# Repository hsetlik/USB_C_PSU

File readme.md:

# USB-C and li-ion power supply

I designed this little power supply board for my ongoing polyphonic synth project. Like most analog synths it needs a +/-12V supply, as well as a 3.3V supply to run a microcontroller and some other digital bits and pieces. It doesn't consume a crazy amount of power, so I thought a built-in battery and the ability to power the synth over USB-C would be nice features. As power supplies go it's a bit complicated, but the circuit is made up of six basic blocks which are each simple enough on their own so I'll go through each one below.

The KiCad files are for both the schematic and the PCB are in this repo along with a PDF of the schematic. There's an interactive BOM file inside the "bom" directory as well.

## Block 1: USB-C connector and PD negotiation

Throughout the revisions of this board I learned the hard way that power over USB-C isn't as simple as routing the VBUS pin to a power input. Devices that recieve power via USB-C PD (power delivery) must "negotiate" with the power source via the connector's two CC pins to request the needed voltage and current. A simple solution here is to connect CC1 and CC2 to ground each through their own 5.1k resistor. This, however limits the device to 500mA at 5V. In order to negotiate our target max power of 3A at 5 volts, we can use a dedicated IC like the [CYPD3177](https://www.infineon.com/dgdl/Infineon-EZ-PD_BCR_Datasheet_USB_Type-C_Port_Controller_for_Power_Sinks-DataSheet-v03_00-EN.pdf?fileId=8ac78c8c7d0d8da4017d0ee7ce9d70ad), which connects to our CC pins and negotiates for voltage and current values which are set by some resistor dividers. [This video](https://www.youtube.com/watch?v=W13HNsoHj7A&t=1458s) by Phil's Lab on YouTube is a great explanation of this IC and how to work with USB-C in general. The IC operates a MOSFET load switch (Q102 on the schematic) to connect the input 5V line to our VDD net when negotiation is successful.

## Block 2: Battery charger

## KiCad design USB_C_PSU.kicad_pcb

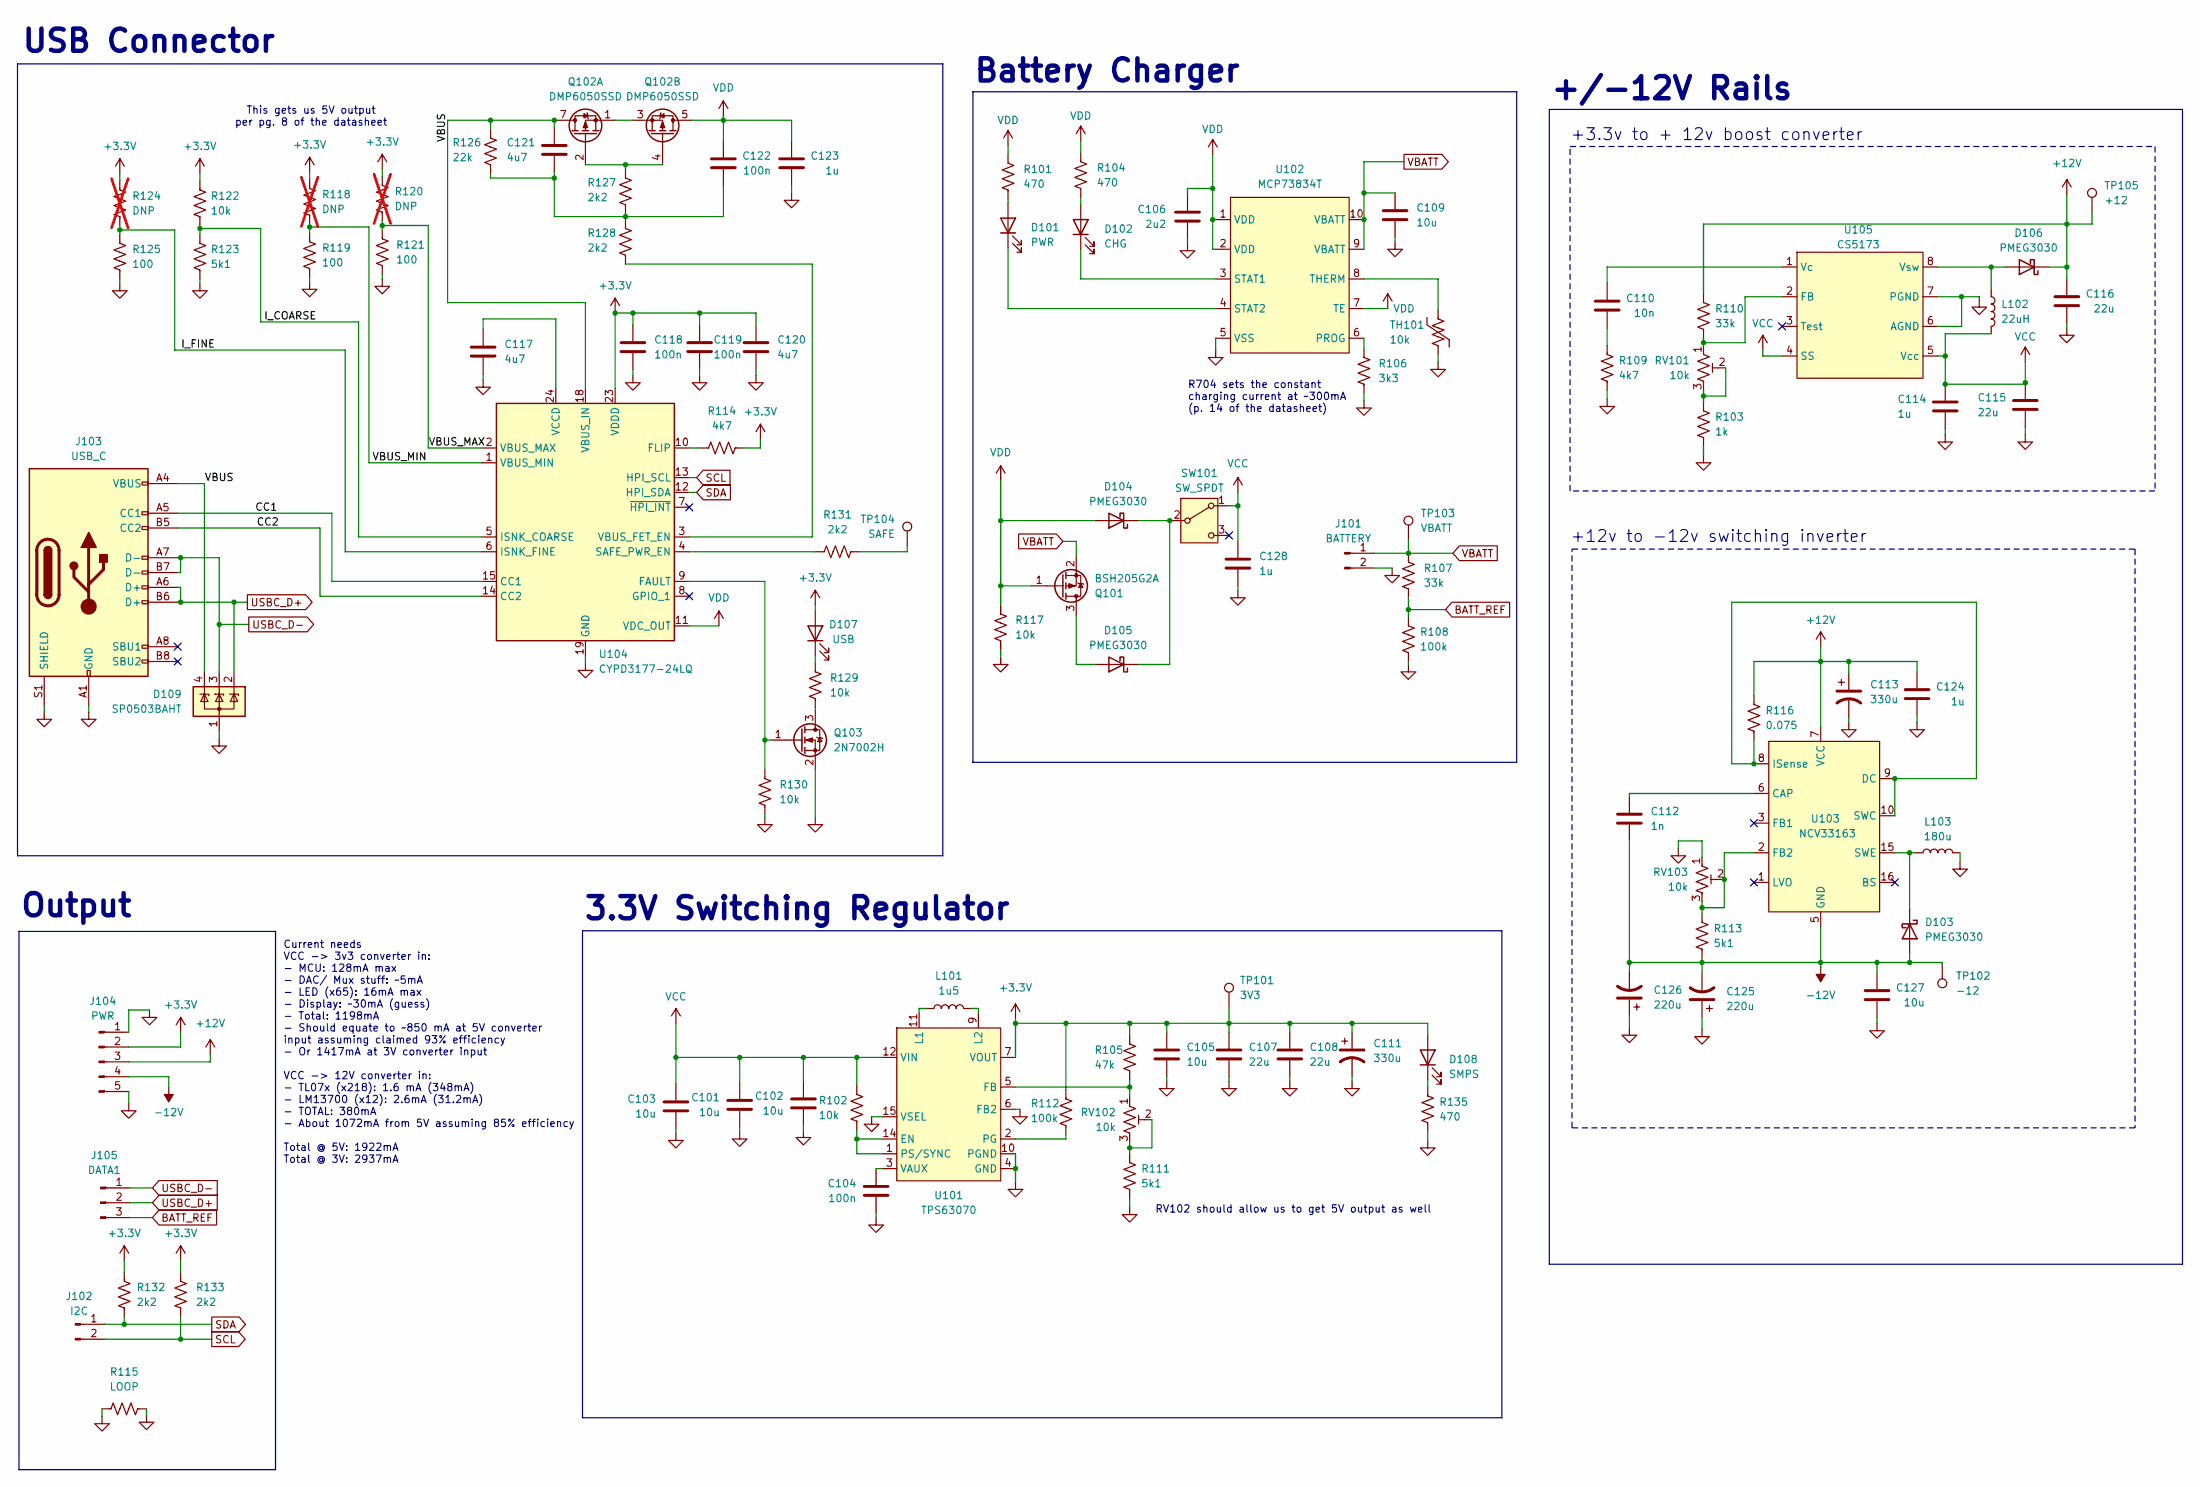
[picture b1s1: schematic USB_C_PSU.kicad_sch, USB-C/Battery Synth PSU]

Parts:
C101, C102, C103, C105, C109, C127: 10u; C_0805_2012Metric
C104, C118, C119, C122: 100n; C_0805_2012Metric
C106: 2u2; C_0805_2012Metric
C107, C108, C115, C116: 22u; C_0805_2012Metric
C110: 10n; C_0805_2012Metric
C111, C113: 330u; CP_Radial_D5.0mm_P2.50mm
C112: 1n; C_0805_2012Metric
C114, C123, C124, C128: 1u; C_0805_2012Metric
C117, C120, C121: 4u7; C_0805_2012Metric
C125, C126: 220u; CP_Radial_D5.0mm_P2.50mm
D101: PWR; LED_D3.0mm
D102: CHG; LED_D3.0mm
D103, D104, D105, D106: PMEG3030; D_SOD-123
D107: USB; LED_D3.0mm
D108: SMPS; LED_D3.0mm
D109: SP0503BAHT; SOT-143
J101: BATTERY; PinHeader_1x02_P2.54mm_Vertical
J102: I2C; PinHeader_1x02_P2.54mm_Vertical
J103: USB_C; USB_C_Receptacle_Palconn_UTC16-G
J104: PWR; PinHeader_1x05_P2.54mm_Vertical
J105: DATA1; PinHeader_1x03_P2.54mm_Vertical
L101: 1u5; L_Coilcraft_XAL4020-XXX
L102: 22uH; L_Changjiang_FNR4010S
L103: 180u; L_Coilcraft_MSS1278-XXX
Q101: BSH205G2A; SOT-23
Q102: DMP6050SSD; SOIC-8_3.9x4.9mm_P1.27mm
Q103: 2N7002H; SOT-23
R101, R104, R135: 470; R_0805_2012Metric
R102, R117, R122, R129, R130: 10k; R_0805_2012Metric
R103: 1k; R_0805_2012Metric
R105: 47k; R_0805_2012Metric
R106: 3k3; R_0805_2012Metric
R107, R110: 33k; R_0805_2012Metric
R108, R112: 100k; R_0805_2012Metric
R109, R114: 4k7; R_0805_2012Metric
R111, R113, R123: 5k1; R_0805_2012Metric
R115: LOOP; R_Axial_DIN0204_L3.6mm_D1.6mm_P5.08mm_Horizontal
R116: 0.075; R_0805_2012Metric
R118, R120, R124: DNP; R_0805_2012Metric; not fitted
R119, R121, R125: 100; R_0805_2012Metric
R126: 22k; R_0805_2012Metric
R127, R128, R131, R132, R133: 2k2; R_0805_2012Metric
RV101, RV102, RV103: 10k; Potentiometer_Bourns_3296W_Vertical
SW101: SW_SPDT; SW_NKK_B12JH_SPDT
TH101: 10k; R_0603_1608Metric
TP101: 3V3; TestPoint_THTPad_D1.0mm_Drill0.5mm_VAL
TP102: -12; TestPoint_THTPad_D1.0mm_Drill0.5mm_VAL
TP103: VBATT; TestPoint_THTPad_D1.0mm_Drill0.5mm_VAL
TP104: SAFE; TestPoint_THTPad_D1.0mm_Drill0.5mm_VAL
TP105: +12; TestPoint_THTPad_D1.0mm_Drill0.5mm_VAL
U101: TPS63070; TXN_QFN15
U102: MCP73834T; MSOP-10_3x3mm_P0.5mm
U103: NCV33163; SOIC-16W_7.5x10.3mm_P1.27mm
U104: CYPD3177-24LQ; QFN-24-1EP_4x4mm_P0.5mm_EP2.75x2.75mm
U105: CS5173; SOIC-8_3.9x4.9mm_P1.27mm

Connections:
+3.3V: C105.1, C107.1, C108.1, C111.1, C118.1, C119.1, C120.1, D107.2 (A), D108.2 (A), J104.2, R105.1, R112.1, R114.2, R118.1, R120.1, R122.1, R124.1, R132.1, R133.1, TP101.1, U101.7 (VOUT), U101.8 (VOUT), U104.23 (VDDD)
+12V: C113.1, C116.1, C124.1, D106.1 (K), J104.3, R110.1, R116.1, TP105.1, U103.7 (VCC)
-12V: C112.2, C125.2, C126.2, C127.1, D103.2 (A), J104.4, R113.2, TP102.1, U103.4 (GND), U103.5 (GND), U103.12 (GND), U103.13 (GND)
/CC1: J103.A5 (CC1), U104.15 (CC1)
/CC2: J103.B5 (CC2), U104.14 (CC2)
/I_COARSE: R122.2, R123.1, U104.5 (ISNK_COARSE)
/I_FINE: R124.2, R125.1, U104.6 (ISNK_FINE)
/VBUS: C121.1, D109.4 (K), J103.A4 (VBUS), J103.A9 (VBUS), J103.B4 (VBUS), J103.B9 (VBUS), Q102.7 (D1), Q102.8 (D1), R126.1, U104.18 (VBUS_IN)
/VBUS_MAX: R120.2, R121.1, U104.2 (VBUS_MAX)
/VBUS_MIN: R118.2, R119.1, U104.1 (VBUS_MIN)
BATT_REF: J105.3, R107.2, R108.1
GND: C101.2, C102.2, C103.2, C104.2, C105.2, C106.2, C107.2, C108.2, C109.2, C111.2, C113.2, C114.2, C115.2, C116.2, C117.2, C118.2, C119.2, C120.2, C123.2, C124.2, C125.1, C126.1, C127.2, C128.2, D109.1 (A), J101.2, J103.A1 (GND), J103.A12 (GND), J103.B1 (GND), J103.B12 (GND), J103.S1 (SHIELD), J104.1, J104.5, L103.2, Q103.2 (S), R103.2, R106.2, R108.2, R109.2, R111.2, R115.1, R115.2, R117.2, R119.2, R121.2, R123.2, R125.2, R130.2, R135.2, RV103.1, TH101.2, U101.4 (GND), U101.6 (FB2), U101.10 (PGND), U101.15 (VSEL), U102.5 (VSS), U104.19 (GND), U104.22 (GND), U104.25 (GND), U105.6 (AGND), U105.7 (PGND)
unnamed: C110.2, R109.1
unnamed: C121.2, C122.2, R126.2, R127.2, R128.1
unnamed: D101.2 (A), R101.2
unnamed: D101.1 (K), U102.4 (STAT2)
unnamed: D102.2 (A), R104.2
unnamed: D102.1 (K), U102.3 (STAT1)
unnamed: D103.1 (K), L103.1, U103.14 (SWE), U103.15 (SWE)
unnamed: D104.1 (K), D105.1 (K), SW101.2 (B)
unnamed: D105.2 (A), Q101.3 (D)
unnamed: D106.2 (A), L102.1, U105.8 (Vsw)
unnamed: D107.1 (K), R129.1
unnamed: D108.1 (K), R135.1
unnamed: Q102.2 (G1), Q102.4 (G2), R127.1
unnamed: Q102.1 (S1), Q102.3 (S2)
unnamed: Q103.3 (D), R129.2
unnamed: Q103.1 (G), R130.1, U104.9 (FAULT)
unnamed: R103.1, RV101.2, RV101.3
unnamed: R111.1, RV102.2, RV102.3
unnamed: R131.2, TP104.1
unnamed: R102.2, U101.1 (PS/SYNC), U101.14 (EN)
unnamed: R105.2, RV102.1, U101.5 (FB)
unnamed: L101.1, U101.11 (L1)
unnamed: L101.2, U101.9 (L2)
unnamed: R112.2, U101.2 (PG)
unnamed: C104.1, U101.3 (VAUX)
unnamed: R106.1, U102.6 (PROG)
unnamed: TH101.1, U102.8 (THERM)
unnamed: C112.1, U103.6 (CAP)
unnamed: R116.2, U103.8 (ISense), U103.9 (DC), U103.10 (SWC), U103.11 (SWC)
unnamed: R113.1, RV103.2, RV103.3, U103.2 (FB2)
unnamed: R114.1, U104.10 (FLIP)
unnamed: R131.1, U104.4 (SAFE_PWR_EN)
unnamed: R128.2, U104.3 (VBUS_FET_EN)
unnamed: C117.1, U104.24 (VCCD)
unnamed: R110.2, RV101.1, U105.2 (FB)
unnamed: C110.1, U105.1 (Vc)
SCL: J102.2, R133.2, U104.13 (HPI_SCL)
SDA: J102.1, R132.2, U104.12 (HPI_SDA)
USBC_D+: D109.2 (K), J103.A6 (D+), J103.B6 (D+), J105.2
USBC_D-: D109.3 (K), J103.A7 (D-), J103.B7 (D-), J105.1
VBATT: C109.1, J101.1, Q101.2 (S), R107.1, TP103.1, U102.9 (VBATT), U102.10 (VBATT)
VCC: C101.1, C102.1, C103.1, C114.1, C115.1, C128.1, L102.2, R102.1, SW101.1 (A), U101.12 (VIN), U101.13 (VIN), U105.4 (SS), U105.5 (Vcc)
VDD: C106.1, C122.1, C123.1, D104.2 (A), Q101.1 (G), Q102.5 (D2), Q102.6 (D2), R101.1, R104.1, R117.1, U102.1 (VDD), U102.2 (VDD), U102.7 (TE), U104.11 (VDC_OUT)

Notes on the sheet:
This gets us 5V output per pg. 8 of the datasheet
3.3V Switching Regulator
Current needs VCC -> 3v3 converter in: - MCU: 128mA max - DAC/ Mux stuff: ~5mA - LED (x65): 16mA max - Display: ~30mA (guess) - Total: 1198mA - Should equate to ~850 mA at 5V converter input assuming claimed 93% efficiency - Or 1417mA at 3V converter input VCC -> 12V converter in: - TL07x (x218): 1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
RV102 should allow us to get 5V output as well
R704 sets the constant charging current at ~300mA (p. 14 of the datasheet)
Output
Battery Charger
USB Connector
+12v to -12v switching inverter
+3.3v to + 12v boost converter
+/-12V Rails

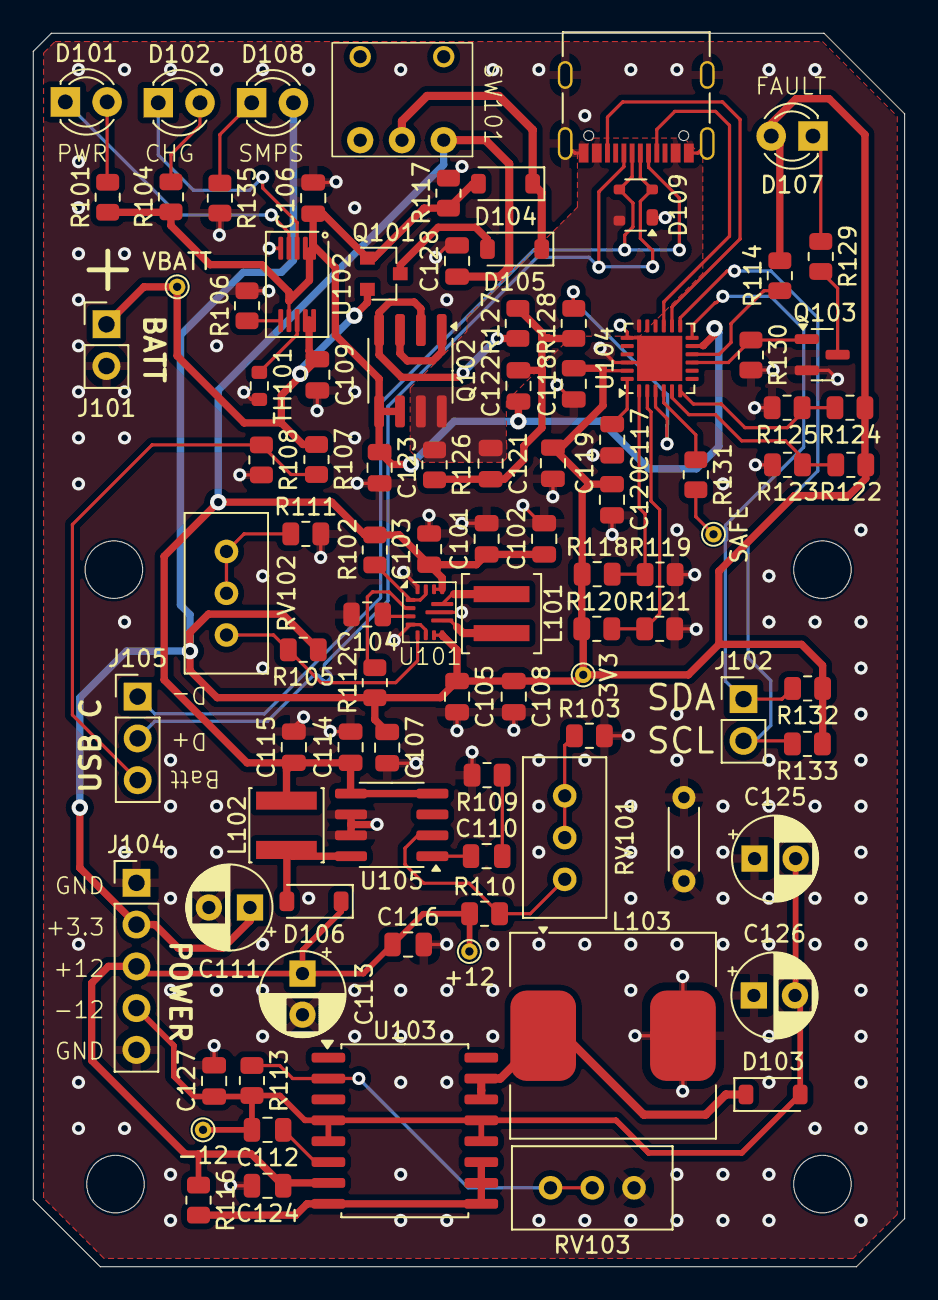
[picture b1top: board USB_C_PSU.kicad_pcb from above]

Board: 4 copper layers, 53.0 x 75.0 mm, 97 parts (0 on the bottom side), 55 nets.

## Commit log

2024-08-25 pdf and readme file
2024-08-25 finished readme
